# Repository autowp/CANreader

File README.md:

# CANreader

CANreader is an Android client for monitoring and transmitting CAN frames through a compatible adapter. It uses the CanHacker protocol; it is not a generic OBD-II or ELM327 application.

The app supports standard 11-bit and extended 29-bit CAN identifiers, data and remote-transmission-request (RTR) frames, a receive monitor, and transmit lists. It can import and export CanHacker `.txl` transmit-list files.

## Requirements

- Android 6.0 (API 23) or later.
- A CAN adapter that implements the CanHacker protocol.
- USB host/OTG is needed only when using a USB serial adapter. Bluetooth Classic SPP and UDP network connections are also available; a loopback connection is provided for testing.

See the [English documentation](docs/en/README.md) or [Russian documentation](docs/ru/README.md) for adapter and hardware details.

## Build

Install JDK 17 or newer, Android SDK Platform 37, and Android SDK Build-Tools 37.0.0. Open this directory in Android Studio and allow Gradle to sync. The project uses Gradle 9.8.0 and Android Gradle Plugin 9.4.1; dependency versions are managed in `gradle/libs.versions.toml`.

The Android, Java, Gradle, and XML extensions are listed in `.vscode/extensions.json`. Keep machine-specific SDK paths in the ignored `local.properties` file.

Run these commands from the repository root:

```sh
./gradlew assembleDebug
./gradlew testDebugUnitTest
./gradlew lintDebug
```

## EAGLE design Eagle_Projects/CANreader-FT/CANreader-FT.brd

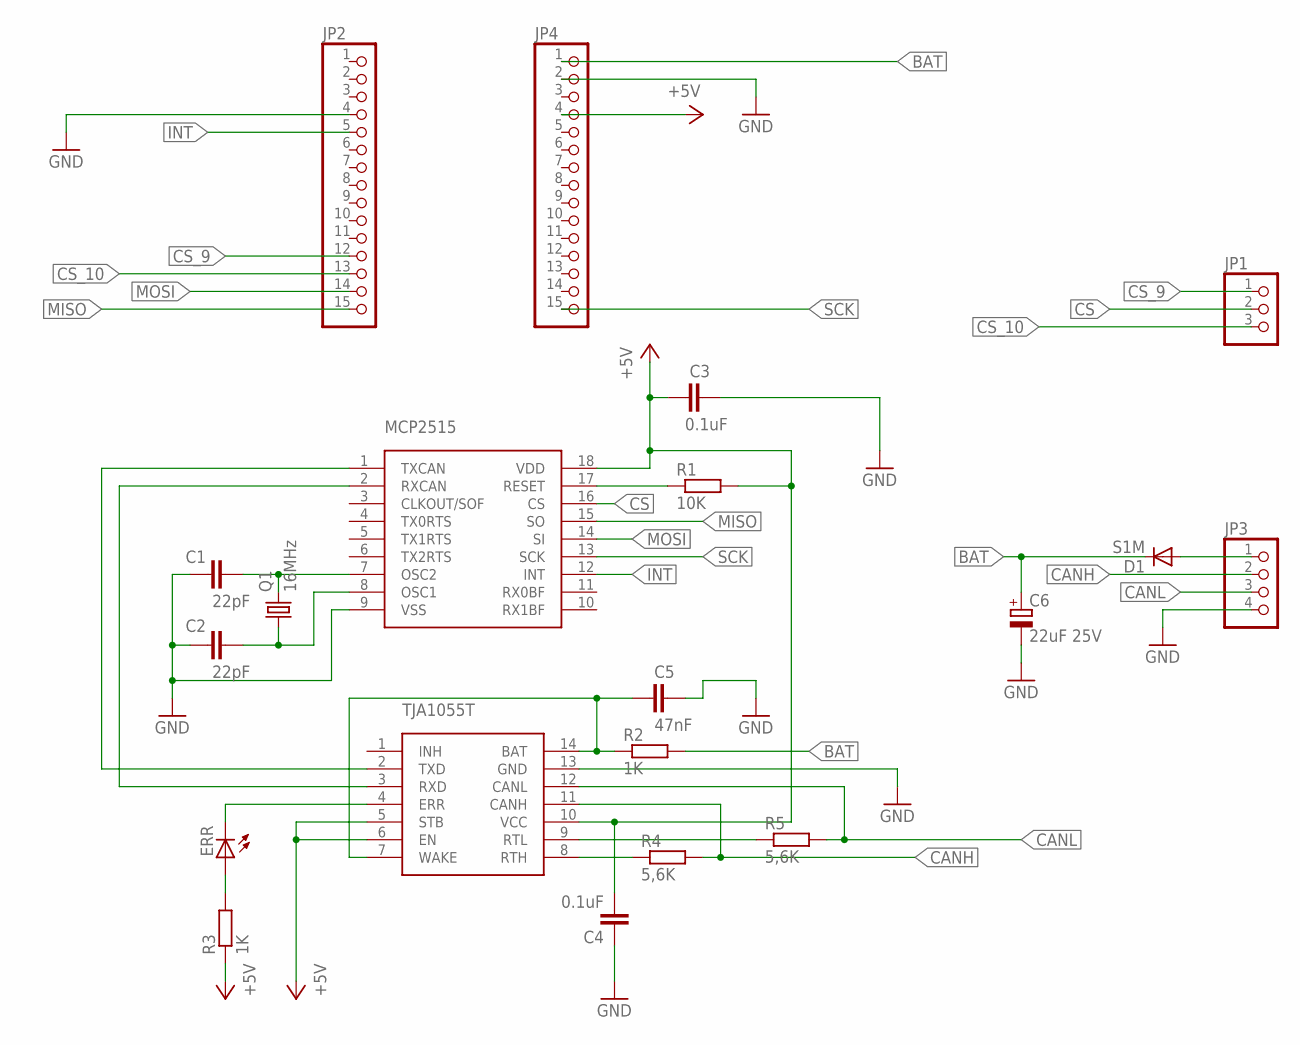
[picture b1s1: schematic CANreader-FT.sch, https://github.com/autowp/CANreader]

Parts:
C1, C2: 22pF; C0805
C3, C4: 0.1uF; C0805
C5: 47nF; C0805
C6: 22uF 25V; SMC_C
D1: S1M; SMA
ERR: LEDCHIP-LED0805; CHIP-LED0805
JP1: PINHD-1X3; 1X03
JP2, JP4: PINHD-1X15; 1X15
JP3: PINHD-1X4-1; 1X04
MCP2515: MCP2515; SO18-1
Q1: 16MHz; HC49/S
R1: 10K; R0805
R2, R3: 1K; R0805
R4, R5: 5,6K; R0805
TJA1055T: TJA1055T; SO-14W

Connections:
+5V: C3.1, C4.2, JP4.4, MCP2515.18 (VDD), R1.2, R3.1, TJA1055T.5 (STB), TJA1055T.6 (EN), TJA1055T.10 (VCC)
BAT: C6.+, D1.C, JP4.1, R2.2
CANH: JP3.2, R4.2, TJA1055T.11 (CANH)
CANL: JP3.3, R5.2, TJA1055T.12 (CANL)
CS: JP1.2, MCP2515.16 (CS)
CS_9: JP1.1, JP2.12
CS_10: JP1.3, JP2.13
GND: C1.1, C2.1, C3.2, C4.1, C5.2, C6.-, JP2.4, JP3.4, JP4.2, MCP2515.9 (VSS), TJA1055T.13 (GND)
INT: JP2.5, MCP2515.12 (INT)
MISO: JP2.15, MCP2515.15 (SO)
MOSI: JP2.14, MCP2515.14 (SI)
unnamed: MCP2515.1 (TXCAN), TJA1055T.2 (TXD)
unnamed: MCP2515.2 (RXCAN), TJA1055T.3 (RXD)
unnamed: C1.2, MCP2515.7 (OSC2), Q1.2
unnamed: D1.A, JP3.1
unnamed: C2.2, MCP2515.8 (OSC1), Q1.1
unnamed: C5.1, R2.1, TJA1055T.7 (WAKE), TJA1055T.14 (BAT)
unnamed: MCP2515.17 (RESET), R1.1
unnamed: R4.1, TJA1055T.8 (RTH)
unnamed: R5.1, TJA1055T.9 (RTL)
unnamed: ERR.C, TJA1055T.4 (ERR)
unnamed: ERR.A, R3.2
SCK: JP4.15, MCP2515.13 (SCK)

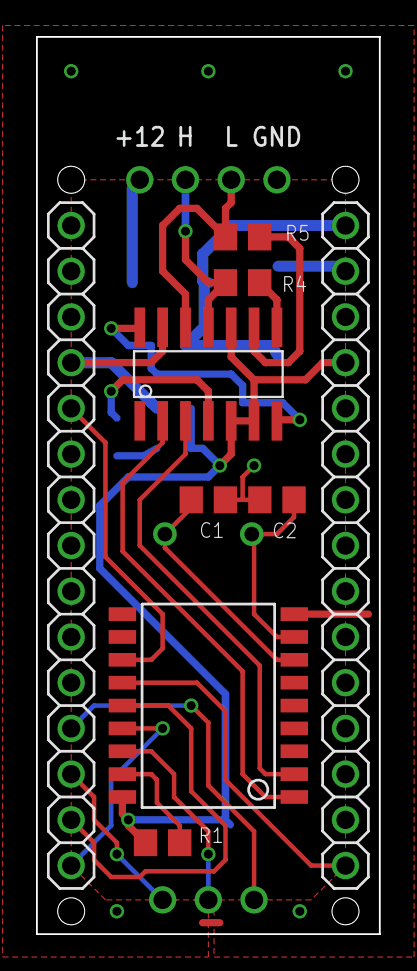
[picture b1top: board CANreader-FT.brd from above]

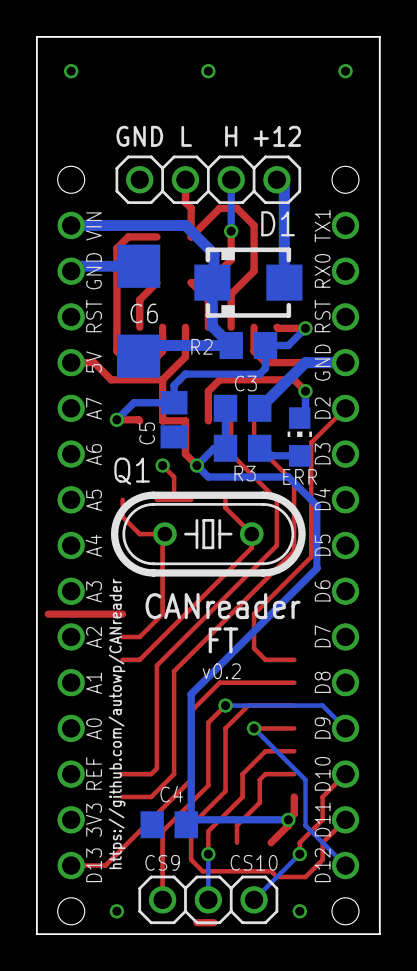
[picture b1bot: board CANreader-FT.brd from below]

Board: 2 copper layers, 19.0 x 49.8 mm, 20 parts (11 on the bottom side), 23 nets.

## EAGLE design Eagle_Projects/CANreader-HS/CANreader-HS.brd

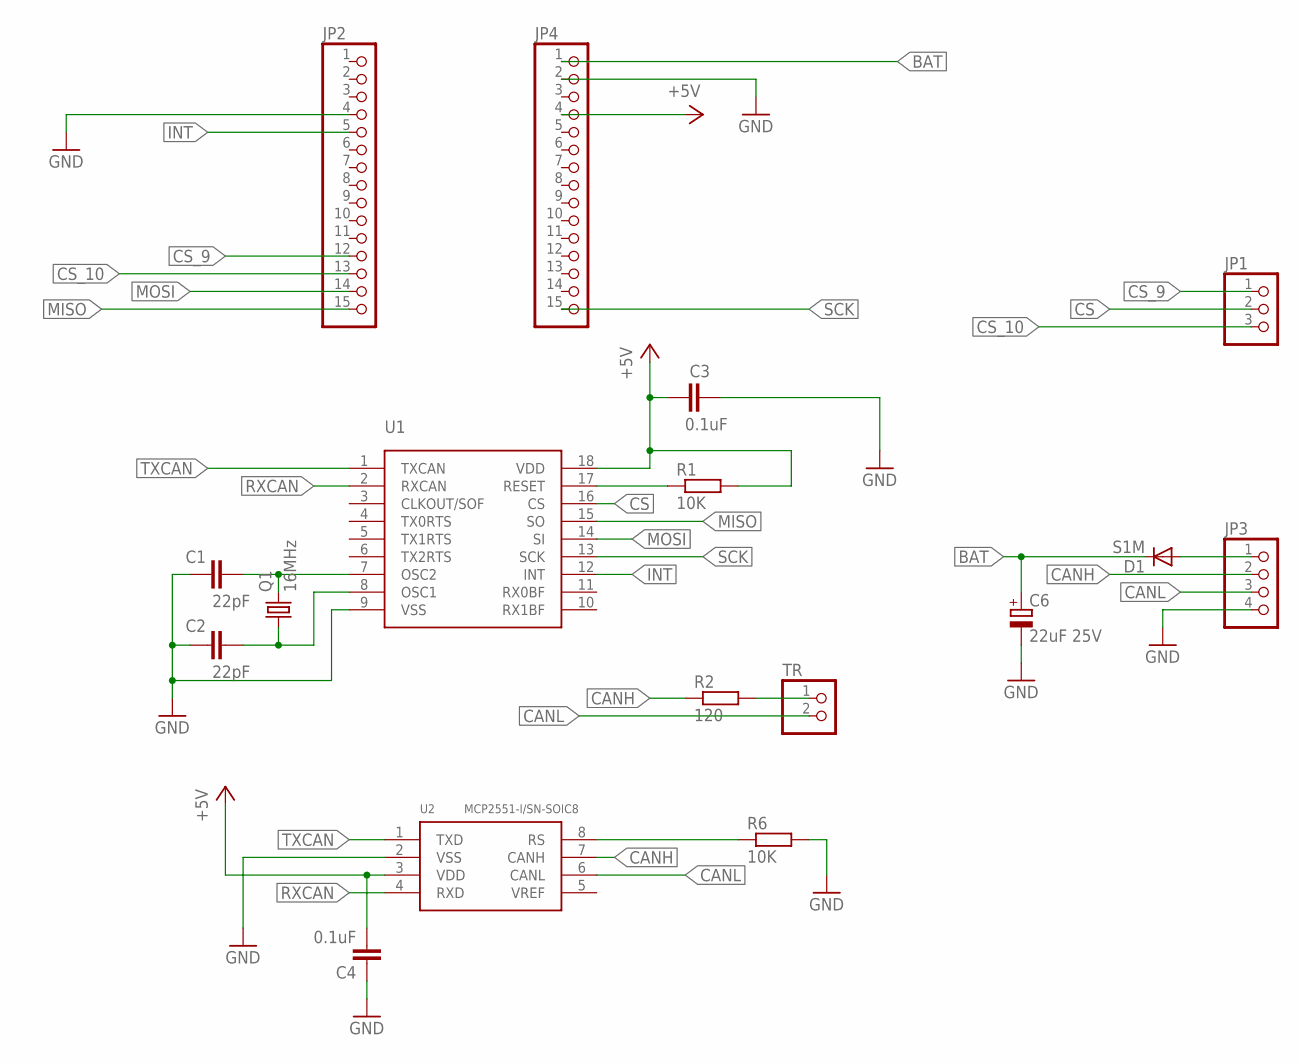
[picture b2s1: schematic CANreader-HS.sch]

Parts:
C1, C2: 22pF; C0805
C3, C4: 0.1uF; C0805
C6: 22uF 25V; SMC_C
D1: S1M; SMA
JP1: PINHD-1X3; 1X03
JP2, JP4: PINHD-1X15; 1X15
JP3: PINHD-1X4-1; 1X04
Q1: 16MHz; HC49/S
R1, R6: 10K; R0805
R2: 120; R0805
TR: PINHD-1X2; 1X02
U1: MCP2515; SO18-1
U2: MCP2551-I/SN-SOIC8; SOIC8-1.27-5X4MM

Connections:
+5V: C3.1, C4.2, JP4.4, R1.2, U1.18 (VDD), U2.3 (VDD)
BAT: C6.+, D1.C, JP4.1
CANH: JP3.2, R2.1, U2.7 (CANH)
CANL: JP3.3, TR.2, U2.6 (CANL)
CS: JP1.2, U1.16 (CS)
CS_9: JP1.1, JP2.12
CS_10: JP1.3, JP2.13
GND: C1.1, C2.1, C3.2, C4.1, C6.-, JP2.4, JP3.4, JP4.2, R6.2, U1.9 (VSS), U2.2 (VSS)
INT: JP2.5, U1.12 (INT)
MISO: JP2.15, U1.15 (SO)
MOSI: JP2.14, U1.14 (SI)
unnamed: R2.2, TR.1
unnamed: C1.2, Q1.2, U1.7 (OSC2)
unnamed: D1.A, JP3.1
unnamed: C2.2, Q1.1, U1.8 (OSC1)
unnamed: R1.1, U1.17 (RESET)
unnamed: R6.1, U2.8 (RS)
RXCAN: U1.2 (RXCAN), U2.4 (RXD)
SCK: JP4.15, U1.13 (SCK)
TXCAN: U1.1 (TXCAN), U2.1 (TXD)

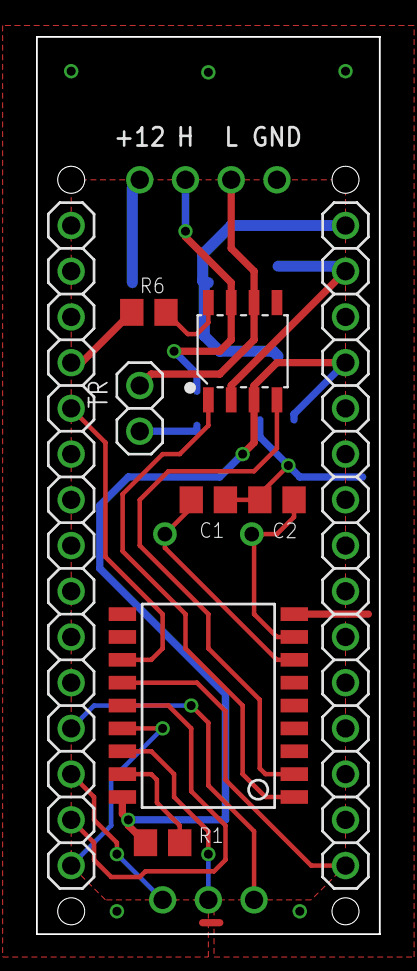
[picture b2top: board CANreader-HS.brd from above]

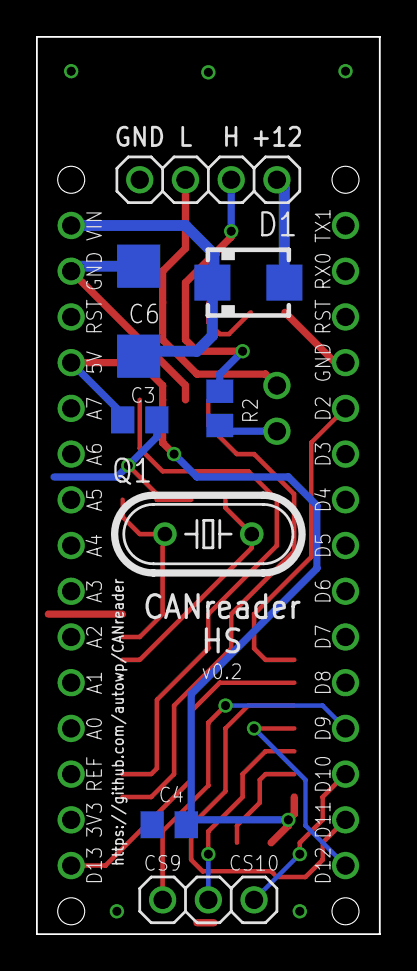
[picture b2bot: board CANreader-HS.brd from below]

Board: 2 copper layers, 19.0 x 49.8 mm, 17 parts (8 on the bottom side), 20 nets.

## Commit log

2016-02-17 gitignore
2016-02-18 RTR Extended ID in monitor Simplify CanHacker command build
2016-02-19 Rename service, save baudrate selection
2016-02-22 Async connection. Sync blocking canhacker commands
2016-02-22 4.x compatibility
2016-02-22 pre JB MR1 readNow
2016-02-22 Change transmit speed on the fly
2016-02-22 Remove manifest-based usb persmissions
2016-02-28 Felhr library update
2016-02-28 ELM327 proto
2016-02-28 Felhr sync read methods
2016-02-28 Connection: save last selected device
2016-03-13 UART baudrate configuration
2016-03-13 Version bump
2016-03-13 Icon
2016-03-14 Connection problem Toast. Remove styles
2016-03-15 Revert "aaa"
    This reverts commit 207a7e0748e3f5b5e78aea61d385afd3e113fb09.
2016-03-15 Revert "Revert "aaa""
    This reverts commit f4fbecd6480a20bbb3734ec9b73215f9661af07f.
2016-03-15 Hangs processings
2016-03-15 Move actions from buttons to context menu
2016-03-16 bultTransfer timout fix.
    CH340 compatibility
2016-03-20 Move docs from wiki
2016-03-20 Crosslinks in docs
2016-03-20 Translate EN -> RU
2016-03-20 Schemes
2016-03-20 new 3D model images
2016-03-20 Adapters list rearrange
2016-03-20 Translate word
2016-03-20 Monitor speed meter
2016-03-22 add photo
2016-03-23 txl files
2016-03-23 Copy TX CAN frame
2016-03-23 Copy, delete monitor messages
2016-03-24 Docs / Features
2016-03-25 Loopback adapter
2016-03-25 Android version fix
2016-03-26 Focus activity
2016-04-02 Bluetooth adapter
2016-04-04 Break read thread on errors
2016-04-04 Chnage app name
2016-05-30 Update studio. Smooth period calculation
2016-09-14 Add Eagle Projects
2016-09-14 Rename eagle files
2016-09-14 edit ditignore
2016-09-14 Add hyperlink
2016-09-16 Add PDF
